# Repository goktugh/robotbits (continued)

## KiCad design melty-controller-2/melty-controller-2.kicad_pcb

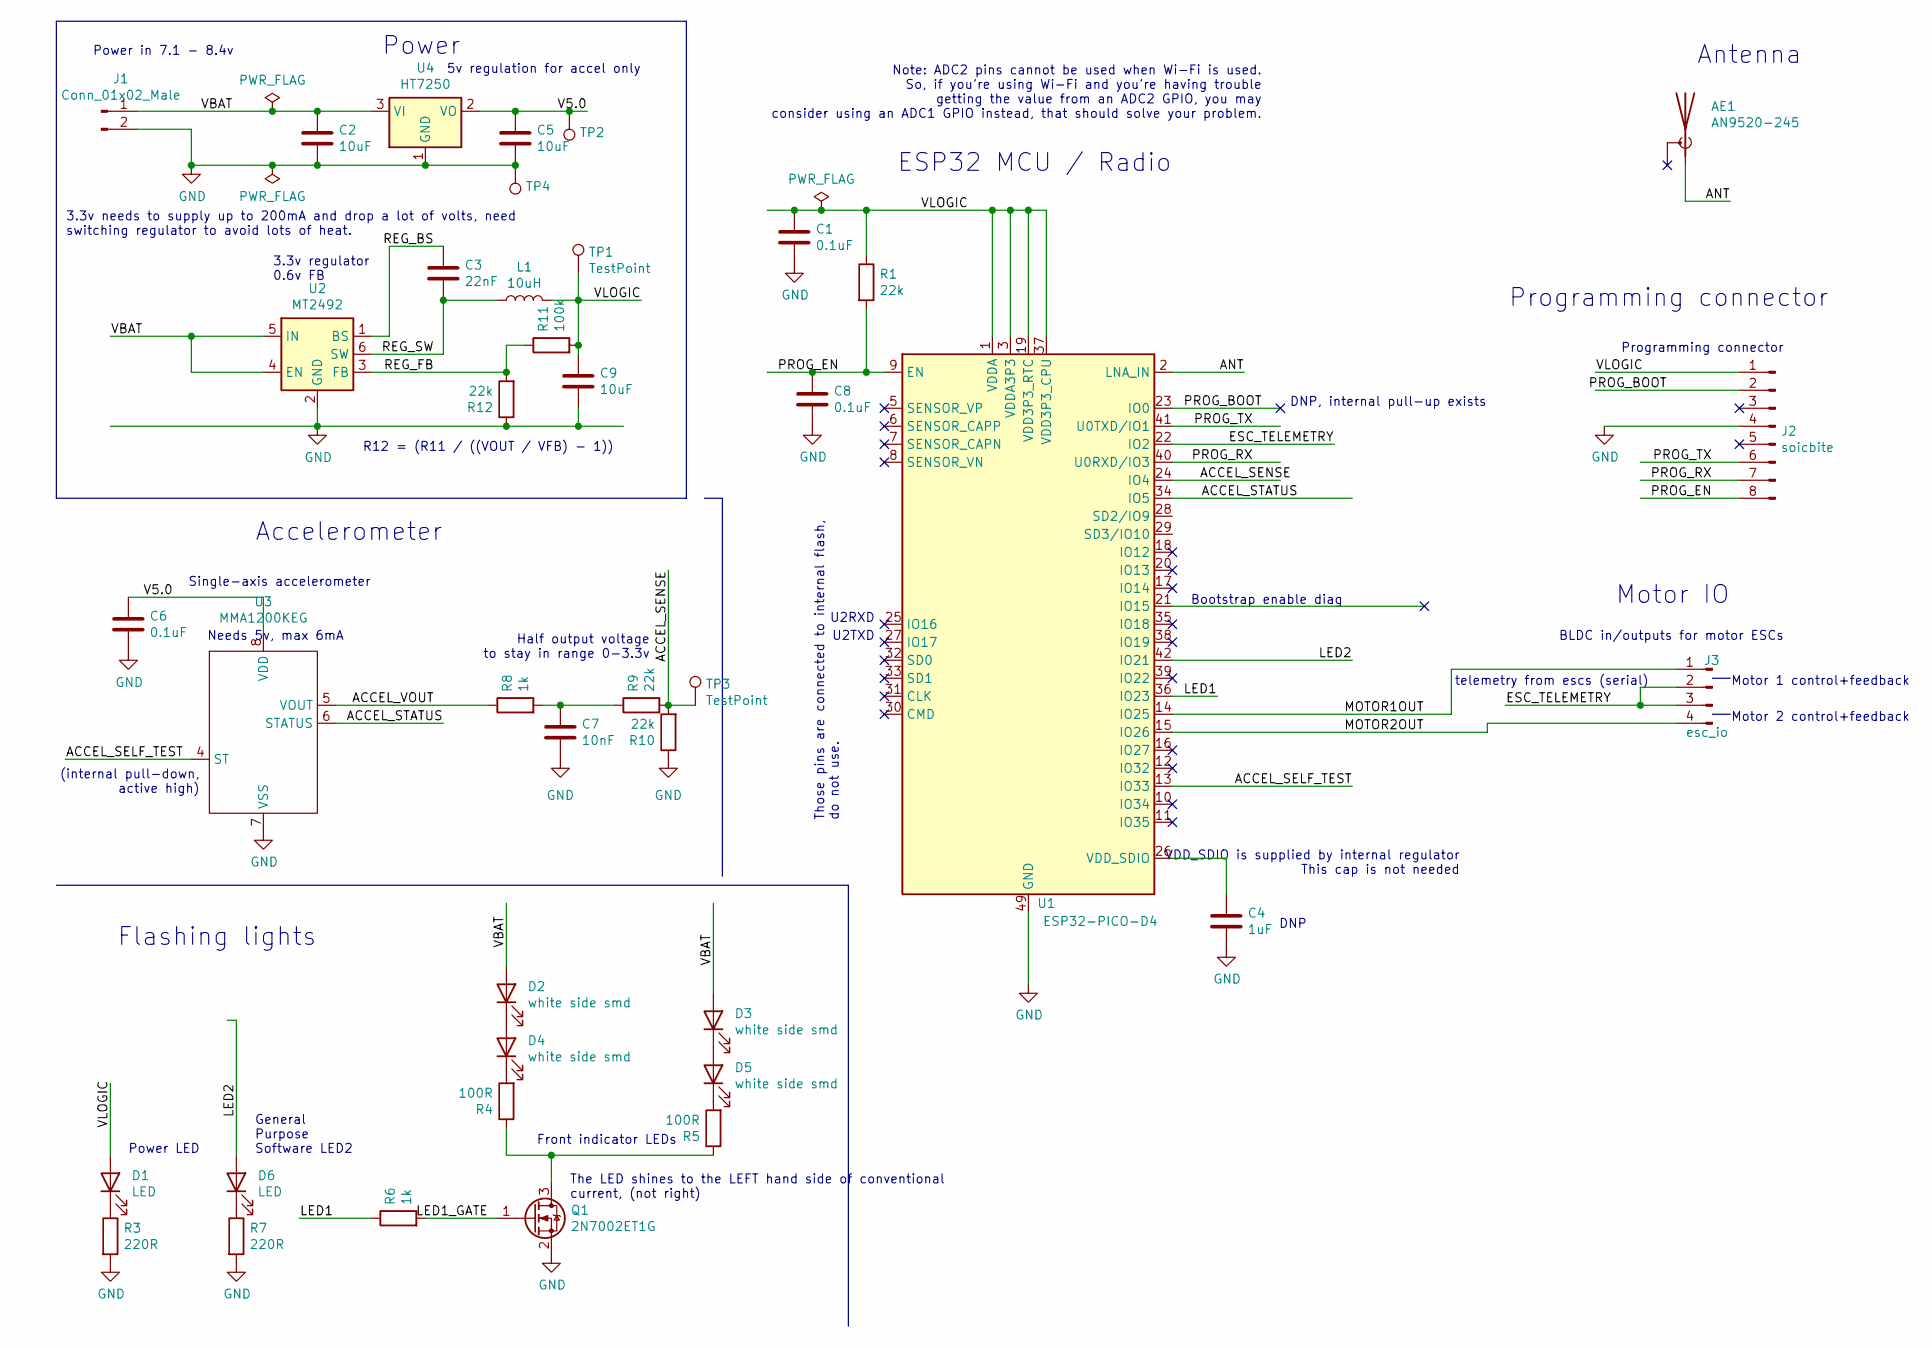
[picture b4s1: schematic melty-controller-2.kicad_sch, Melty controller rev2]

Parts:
AE1: AN9520-245; LCSC C99665
C1, C6, C8: 0.1uF; C_0603_1608Metric; LCSC C1591
C2, C5, C9: 10uF; C_0603_1608Metric; LCSC C19702
C3: 22nF; C_0603_1608Metric; LCSC C21122
C4: 1uF; C_0603_1608Metric; LCSC C15849
C7: 10nF; C_0603_1608Metric; LCSC C1589
D1, D6: LED; LED_0805_2012Metric_Castellated; LCSC C192318
D2, D3, D4, D5: white side smd; LED_SIDEVIEW; LCSC C329181
J1: Conn_01x02_Male; SolderWire-0.5sqmm_1x02_P4.6mm_D0.9mm_OD2.1mm
J2: soicbite; SOIC_clipProgSmall
J3: esc_io; PinHeader_1x04_P2.00mm_Vertical
L1: 10uH; L_1210_3225Metric; LCSC C250231
Q1: 2N7002ET1G; SOT-23; LCSC C71533
R1, R9, R10, R12: 22k; R_0603_1608Metric; LCSC C31850
R3, R7: 220R; R_0603_1608Metric; LCSC C22962
R4, R5: 100R; R_0603_1608Metric; LCSC C22775
R6, R8: 1k; R_0603_1608Metric; LCSC C21190
R11: 100k; R_0603_1608Metric; LCSC C25803
TP1, TP2, TP3, TP4: TestPoint; TestPoint_Pad_1.5x1.5mm
U1: ESP32-PICO-D4; esp32-pico-special; LCSC C193707
U2: MT2492; SOT-23-6; LCSC C89358
U3: MMA1200KEG; SOIC-16W_7.5x10.3mm_P1.27mm
U4: HT7250; SOT-23; LCSC C259602

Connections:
/ACCEL_SELF_TEST: U1.13 (IO33), U3.4 (ST)
/ACCEL_SENSE: R9.2, R10.2, TP3.1, U1.24 (IO4)
/ACCEL_STATUS: U1.34 (IO5), U3.6 (STATUS)
/ACCEL_VOUT: R8.1, U3.5 (VOUT)
/ANT: AE1.1 (A), U1.2 (LNA_IN)
/ESC_TELEMETRY: J3.2, J3.3, U1.22 (IO2)
/LED1: R6.1, U1.36 (IO23)
/LED1_GATE: Q1.1 (G), R6.2
/LED2: D6.2 (A), U1.42 (IO21)
/MOTOR1OUT: J3.1, U1.14 (IO25)
/MOTOR2OUT: J3.4, U1.15 (IO26)
/PROG_BOOT: J2.2, U1.23 (IO0)
/PROG_EN: C8.1, J2.8, R1.2, U1.9 (EN)
/PROG_RX: J2.7, U1.40 (U0RXD/IO3)
/PROG_TX: J2.6, U1.41 (U0TXD/IO1)
/REG_BS: C3.1, U2.1 (BS)
/REG_FB: R11.1, R12.2, U2.3 (FB)
/REG_SW: C3.2, L1.1, U2.6 (SW)
/V5.0: C5.1, C6.1, TP2.1, U3.8 (VDD), U4.2 (VO)
/VBAT: C2.1, D2.2 (A), D3.2 (A), J1.1, U2.4 (EN), U2.5 (IN), U4.3 (VI)
/VLOGIC: C1.1, C9.1, D1.2 (A), J2.1, L1.2, R1.1, R11.2, TP1.1, U1.1 (VDDA), U1.3 (VDDA3P3), U1.4 (VDDA3P3), U1.19 (VDD3P3_RTC), U1.37 (VDD3P3_CPU), U1.43 (VDDA), U1.46 (VDDA)
GND: C1.2, C2.2, C4.2, C5.2, C6.2, C7.2, C8.2, C9.2, J1.2, J2.4, Q1.2 (S), R3.2, R7.2, R10.1, R12.1, TP4.1, U1.49 (GND), U2.2 (GND), U3.7 (VSS), U4.1 (GND)
unnamed: C4.1, U1.26 (VDD_SDIO)
unnamed: C7.1, R8.2, R9.1
unnamed: D1.1 (K), R3.1
unnamed: D2.1 (K), D4.2 (A)
unnamed: D3.1 (K), D5.2 (A)
unnamed: D4.1 (K), R4.2
unnamed: D5.1 (K), R5.2
unnamed: D6.1 (K), R7.1
unnamed: Q1.3 (D), R4.1, R5.1

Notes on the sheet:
3.3v needs to supply up to 200mA and drop a lot of volts, need switching regulator to avoid lots of heat.
Power in 7.1 - 8.4v
(internal pull-down, active high)
Power LED
General Purpose Software LED2
3.3v regulator 0.6v FB
Flashing lights
Needs 5v, max 6mA
Single-axis accelerometer
Accelerometer
Power
The LED shines to the LEFT hand side of conventional current, (not right)
R12 = (R11 / ((VOUT / VFB) - 1))
5v regulation for accel only
Half output voltage to stay in range 0-3.3v
Front indicator LEDs
Those pins are connected to internal flash, do not use.
U2RXD
U2TXD
ESP32 MCU / Radio
Note: ADC2 pins cannot be used when Wi-Fi is used. So, if you’re using Wi-Fi and you’re having trouble getting the value from an ADC2 GPIO, you may consider using an ADC1 GPIO instead, that should solve your problem.
DNP, internal pull-up exists
DNP
Bootstrap enable diag
VDD_SDIO is supplied by internal regulator This cap is not needed
telemetry from escs (serial)
Motor IO
Programming connector
BLDC in/outputs for motor ESCs
Antenna
Motor 1 control+feedback
Motor 2 control+feedback

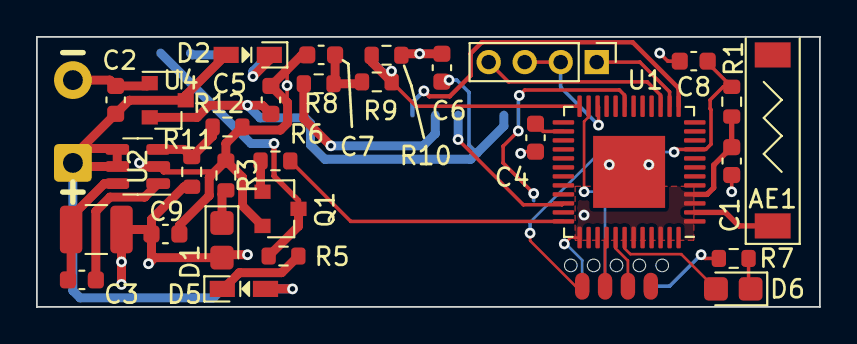
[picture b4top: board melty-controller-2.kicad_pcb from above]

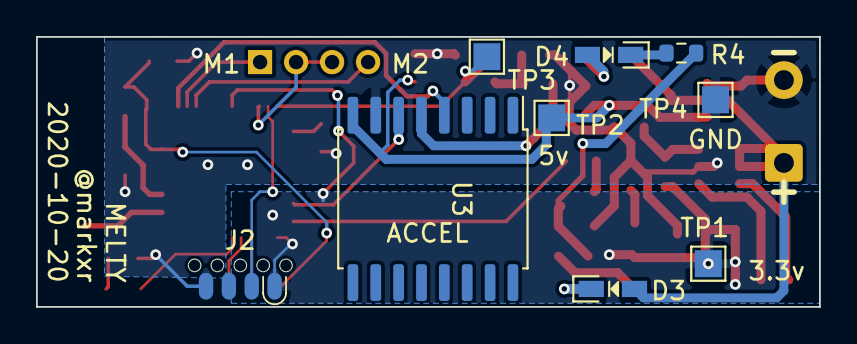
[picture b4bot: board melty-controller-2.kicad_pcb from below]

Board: 2 copper layers, 43.5 x 15.0 mm, 40 parts (9 on the bottom side), 31 nets.

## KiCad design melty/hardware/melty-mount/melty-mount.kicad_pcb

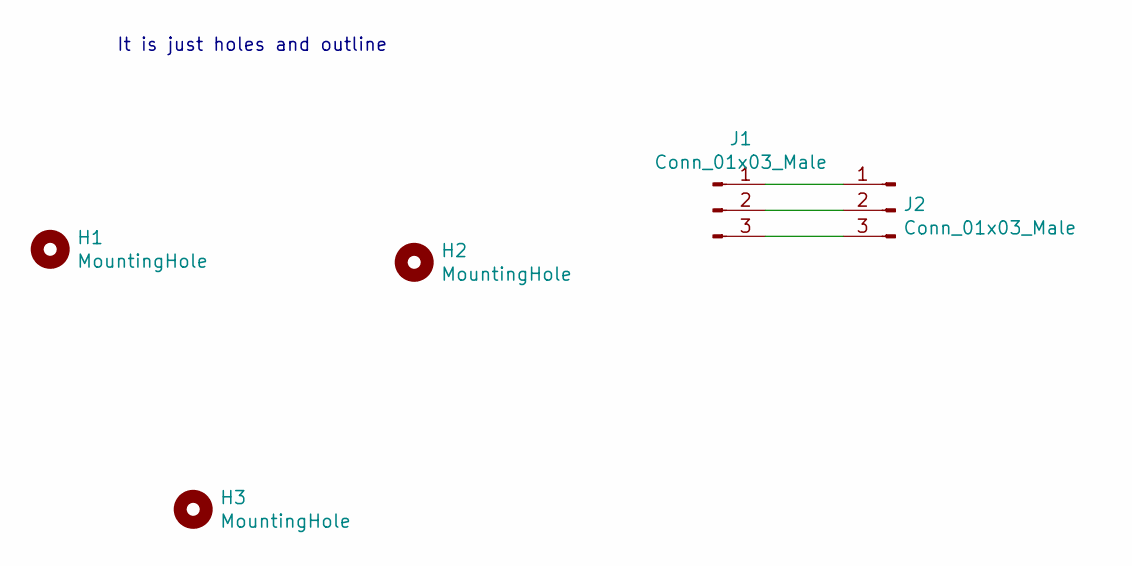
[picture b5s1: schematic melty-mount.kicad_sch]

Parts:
H1, H2: MountingHole; MountingHole_2.2mm_M2
H3: MountingHole; brushlessholes
J1, J2: Conn_01x03_Male; SolderWire-1sqmm_1x03_P5.4mm_D1.4mm_OD2.7mm

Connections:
unnamed: J1.1, J2.1
unnamed: J1.2, J2.2
unnamed: J1.3, J2.3

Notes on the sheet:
It is just holes and outline

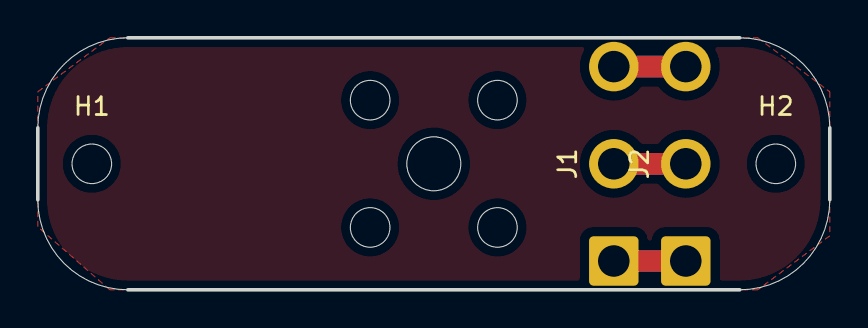
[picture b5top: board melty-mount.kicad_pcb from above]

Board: 2 copper layers, 44.0 x 14.0 mm, 5 parts (0 on the bottom side), 3 nets.
